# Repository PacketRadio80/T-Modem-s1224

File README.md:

# T-Modem-s1224

**Prototype Notice:** This repository contains hardware prototypes that have **passed all automated software tests** (unit, integration, stress). **Practical field testing with real radio equipment is still pending.** Use at your own risk. GPLv3 — non-profit.

---

USB KISS half-TNC + softmodem AFSK for Raspberry Pi Pico. No modem chip — all signal processing done in software (PWM TX / ADC Goertzel RX). Six baud rates available as separate firmware images.

**Firmware language:** C · **License:** GPLv3 · **Platform:** RP2040 (Raspberry Pi Pico)

**Docs:** [`docs/dok/README.md`](docs/dok/README.md) — complete documentation (build · flash · commission · operate · host · troubleshooting).

## Firmware Images

Pre-built UF2 files in `firmware/s1224/bin/`:

| File | Baud | Mark (Hz) | Space (Hz) | Profile |
|------|------|-----------|------------|---------|
| `s1224-300.uf2` | 300 | 1600 | 1800 | HF narrow AFSK |
| `s1224-600.uf2` | 600 | 1200 | 1800 | HF standard |
| `s1224-1200.uf2` | 1200 | 1200 | 2200 | Bell-202 |
| `s1224-2400.uf2` | 2400 | 1775 | 3250 | Y2-class |
| `s1224-3600.uf2` | 3600 | 1800 | 2700 | High-rate HF |
| `s1224-4800.uf2` | 4800 | 2100 | 3300 | High-rate |

Each baud rate requires a **separate firmware image** — no runtime switching.

## Quick Guide — Firmware Update

### Prerequisites
- Raspberry Pi Pico with USB cable
- T-Modem-s1224 board (or any RP2040 board for testing)

### Flash via BOOTSEL (Recommended)

1. **Disconnect** the Pico from USB.
2. **Hold the BOOTSEL button** on the Pico while plugging in USB.
3. The Pico appears as a USB mass storage device (`RPI-RP2`).
4. **Copy** the appropriate `.uf2` file to the `RPI-RP2` drive:
   ```bash
   # Linux
   cp firmware/s1224/bin/s1224-2400.uf2 /media/$USER/RPI-RP2/
   ```
5. The Pico **automatically reboots** and runs the new firmware.
6. Verify: open `/dev/ttyACM0` at 115200 baud, send `STATUS` → should respond.

### Flash via picotool (Advanced)

```bash
picotool load firmware/s1224/bin/s1224-2400.uf2 -x
```

**Unattended (CLI):** send `BOOTSEL` (or `DFU`) to enter the UF2 bootloader, `REBOOT` to restart. Opening the port at **1200 baud** and dropping **DTR** also enters the bootloader (classic 1200bps touch).

### Build from Source

```bash
export PICO_SDK_PATH=/path/to/pico-sdk
cd firmware/s1224
mkdir build && cd build
cmake .. -DS1224_BITRATE=2400   # 300|600|1200|2400|3600|4800
make -j$(nproc)
# → s1224-2400.uf2
```

## Operation

1. Power from **12 V** barrel (centre-positive). USB = data only.
2. Connect USB to host. Open `/dev/ttyACM0` at 115200 baud.
3. **KISS mode:** Send `0xC0`-framed packets (standard KISS TNC).
4. **Service mode:** Send ASCII commands (`HELP`, `STATUS`, `PTT ON/OFF`, `ID`).

### ASCII Commands

| Command | Description |
|---------|-------------|
| `HELP` | List available commands |
| `STATUS` | Show modem state, PTT, signal, bitrate |
| `ID` | Show device ID, callsign, bitrate |
| `PTT ON` / `PTT OFF` | Manual PTT control |
| `QUIET ON/OFF` | Enable/disable unsolicited output |
| `INI` | Dump configuration |
| `GET <key>` | Read config value |
| `SET <key>=<value>` | Set config value (RAM only) |
| `SAVE` | Persist config to flash |
| `RELOAD` | Reload config from flash |
| `DEFAULTS` | Reset to factory defaults |
| `BOOTSEL` / `DFU` | Enter UF2 bootloader (unattended flash) |
| `REBOOT` | Restart the firmware |

## Hardware

- **Schematic:** `hardware/kicad/`
- **BOM:** `hardware/BOM.md` and `hardware/bom/BOM.csv`
- **AF out:** GP6 (PWM AFSK output)
- **AF in:** GP26 (ADC Goertzel input)
- **PTT:** GP9 → optocoupler → radio PTT input
- **Display:** I2C HD44780 via PCF8574 backpack (optional)
- **Missing component (nachrüstbar):** the TX AF output buffer is not populated on the shared AF stage. **Retrofit (Lösung 1):** unity-gain op-amp buffer between the AF source and `RV1` — improves TX audio (required on the c1224's weak TCM3105 `TXA`; optional here since GP6 PWM is a stronger driver).

## Architecture

```
Host (USB CDC) ←→ Pico (RP2040) ←→ Radio
                  │
                  ├── KISS parser (0xC0 framing)
                  ├── HDLC encode/decode
                  ├── AFSK softmodem (PWM TX / Goertzel RX)
                  ├── PTT control (GP9)
                  ├── I2C display (optional)
                  └── Config (flash storage)
```

## Tone Profiles (Compile-Time)

| Baud | Mark (Hz) | Space (Hz) | Shift (Hz) | Notes |
|------|-----------|------------|------------|-------|
| 300 | 1600 | 1800 | 200 | HF narrow |
| 600 | 1200 | 1800 | 600 | HF standard |
| 1200 | 1200 | 2200 | 1000 | Bell-202 |
| 2400 | 1775 | 3250 | 1475 | Y2-class |
| 3600 | 1800 | 2700 | 900 | High-rate HF |
| 4800 | 2100 | 3300 | 1200 | High-rate |

## Project Structure

```
T-Modem-s1224/
├── firmware/s1224/
│   ├── src/common/          # C source files
│   ├── include/             # Headers (afsk_soft.h, afsk_profile.h)
│   ├── config/              # Default INI
│   ├── bin/                 # Pre-built UF2 images (6 rates)
│   └── CMakeLists.txt
├── hardware/
│   ├── kicad/               # Schematic + PCB
│   ├── bom/                 # Bill of materials
│   └── BOM.md
├── docs/                    # User guide, figures
└── share/                   # Example INI files
```

## License

GNU General Public License v3.0 — see [LICENSE](LICENSE).

**Non-profit project.** Not for commercial use without permission.

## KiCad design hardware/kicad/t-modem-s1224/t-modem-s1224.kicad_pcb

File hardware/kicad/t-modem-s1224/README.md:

# KiCad — T-Modem-s1224

Same PCB base as **T-Modem-c1224**, softmodem stuffing / metadata variant.

| File | Role |
|------|------|
| `t-modem-s1224.kicad_sch` | Schematic (chip symbols **DNP**) |
| `t-modem-s1224.kicad_pcb` | PCB **180×180 mm** · **0** tracks · **0** vias |
| `t-modem-s1224.kicad_pro` | Project · `PROJECT=T-Modem-s1224` · `VERSION=1.0-upcoming1` |
| `t-modem-s1224.kicad_sym` | Symbols |
| `t-modem-s1224.rules` | Custom DRC rules |
| `t-modem-s1224.pre-strip-backup.kicad_pcb` | Pre first strip (289 segments) |
| `t-modem-s1224.2026-08-03-pre-reroute-backup.kicad_pcb` | Pre second strip / re-route reset (199 segments) |

## Inventory — PCB footprints (**31**)

**Keep:** U1 Pico · J_DC / U_REG / D_OR1 / F1 / C_BULK / C_BYP* / C_IN · J_AF · Q1 / R_PTT · J_LCD_I2C / U_LVL / RV2 · J_USB / J_USB_PICO · LED_* / R_LED* · SW1 / TP_BOOTSEL · H1–H4.

**Removed (softmodem — not on PCB):**

| Ref | Role |
|-----|------|
| **U_MODEM** / **SKT_MODEM** | TCM3105 + socket (sch **DNP** only) |
| **Y1** / **Y2** / **C_Y*** | Pierce (sch **DNP**) |
| **RV1** / **C_TX** / **C_RX** | Chip-era AF trim / coupling — **DNP** |
| **RV_CDL** / **R_TXR*** / **R_TRS** | Chip straps |

## Schematic DNP (not stuffed)

| Ref | Value | Flags |
|-----|-------|-------|
| **U_MODEM** | TCM3105 | `dnp` · `in_bom no` · `on_board no` |
| **Y1** | 4.4336 MHz | same |
| **Y2** | 6.5536 MHz | same |
| **D_OR2** | DNI-no-VBUS-OR | same (USB VBUS OR unused) |

Tracks (`segment`): **0** — stripped 2026-08-03 for clean re-route.

## U1 Pico AF nets (s1224 — no chip-era `MODEM_*` names)

| Pad | GPIO | Net | Role |
|-----|------|-----|------|
| **9** | GP6 | **`AF_TX`** | PWM AFSK TX → radio AF inject |
| **10** | GP7 | *(NC)* | Unconnected on board |
| **11** | GP8 | *(NC)* | Unconnected on board |
| **31** | GP26 | **`AF_RX`** | ADC RX ← radio AF |
| **12** | GP9 | **`PTT_DRV`** | PTT keying |

## Connector / power nets (pad names)

| Ref | Nets |
|-----|------|
| **J_AF** | `AF_TX` · `AF_RX` · `PTT_OC` · `GND` |
| **J_DC** | `VIN_12` · `GND` ×2 |
| **F1** | `+5V_REG` → `+5V` |
| **D_OR1** | `+5V_OR` ← `+5V` |
| **Q1** / **R_PTT** | `PTT_DRV` → `PTT_B` → `PTT_OC` |

No **`MODEM_*`** · **`TXA`** · **`RXA`** · **`TX_LVL`** on PCB.

## Prototype AF wiring

- **GP6** PWM AFSK out → `AF_TX` → radio inject
- **GP26** ADC0 ← `AF_RX` ← radio RX AF
- **GP9** PTT → `PTT_DRV`

**AS-IS** · GPLv3 · non-profit.

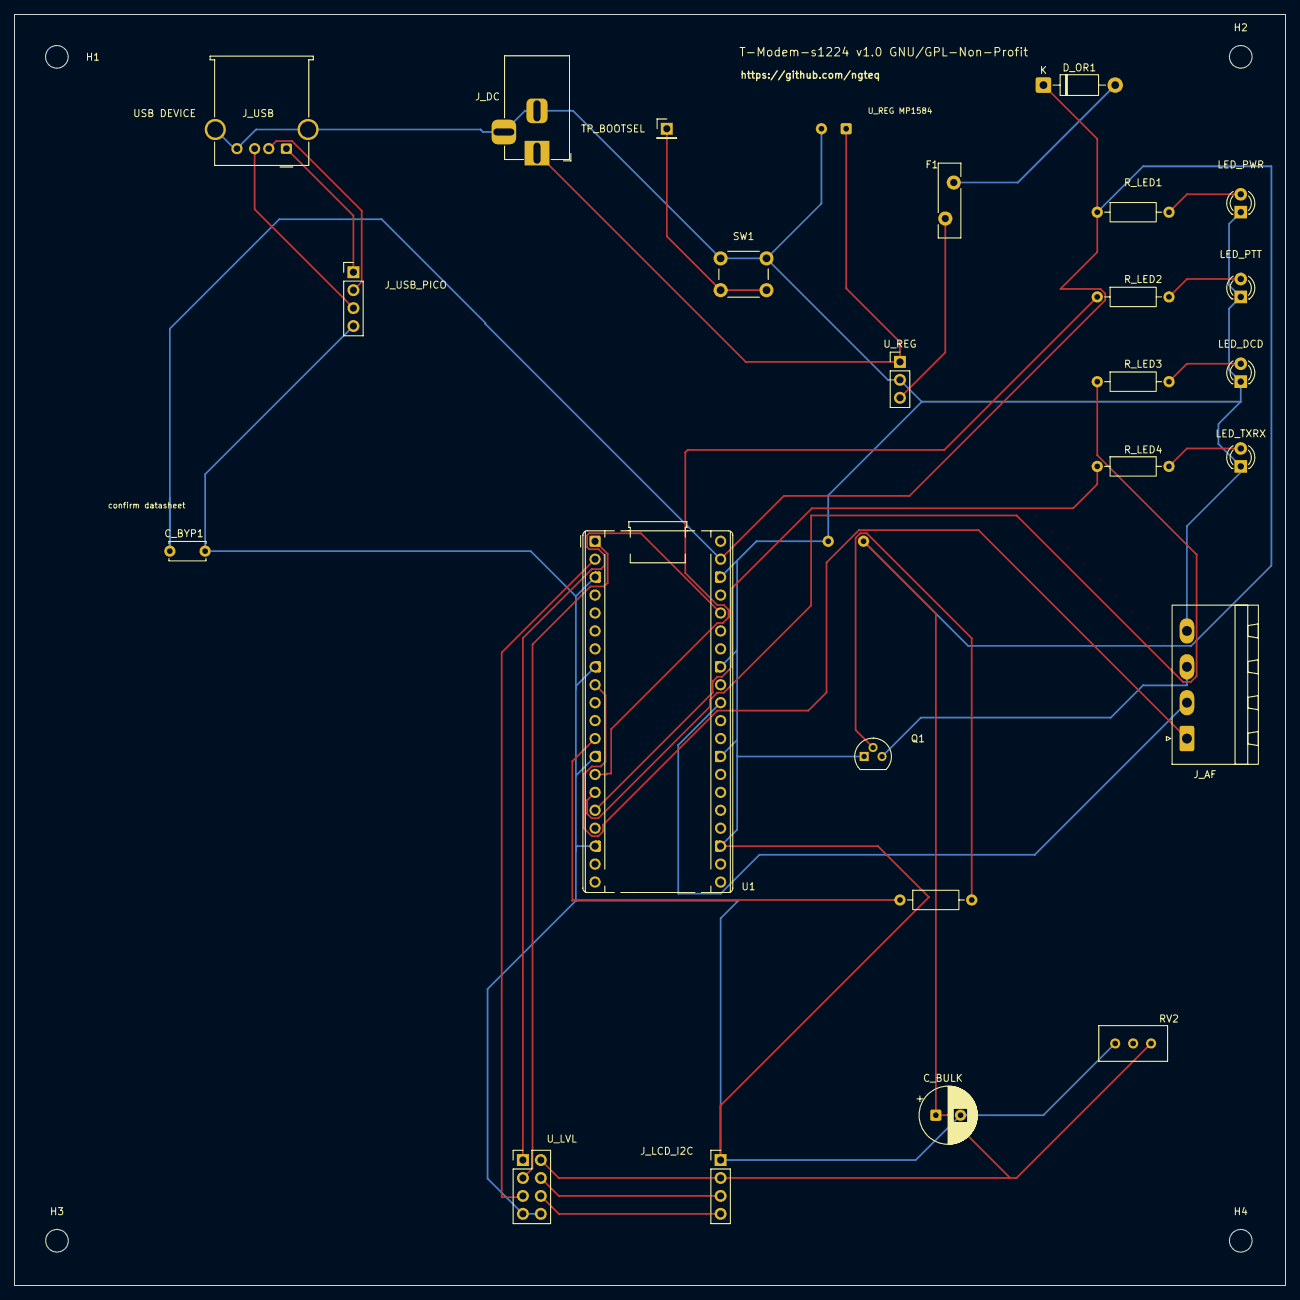
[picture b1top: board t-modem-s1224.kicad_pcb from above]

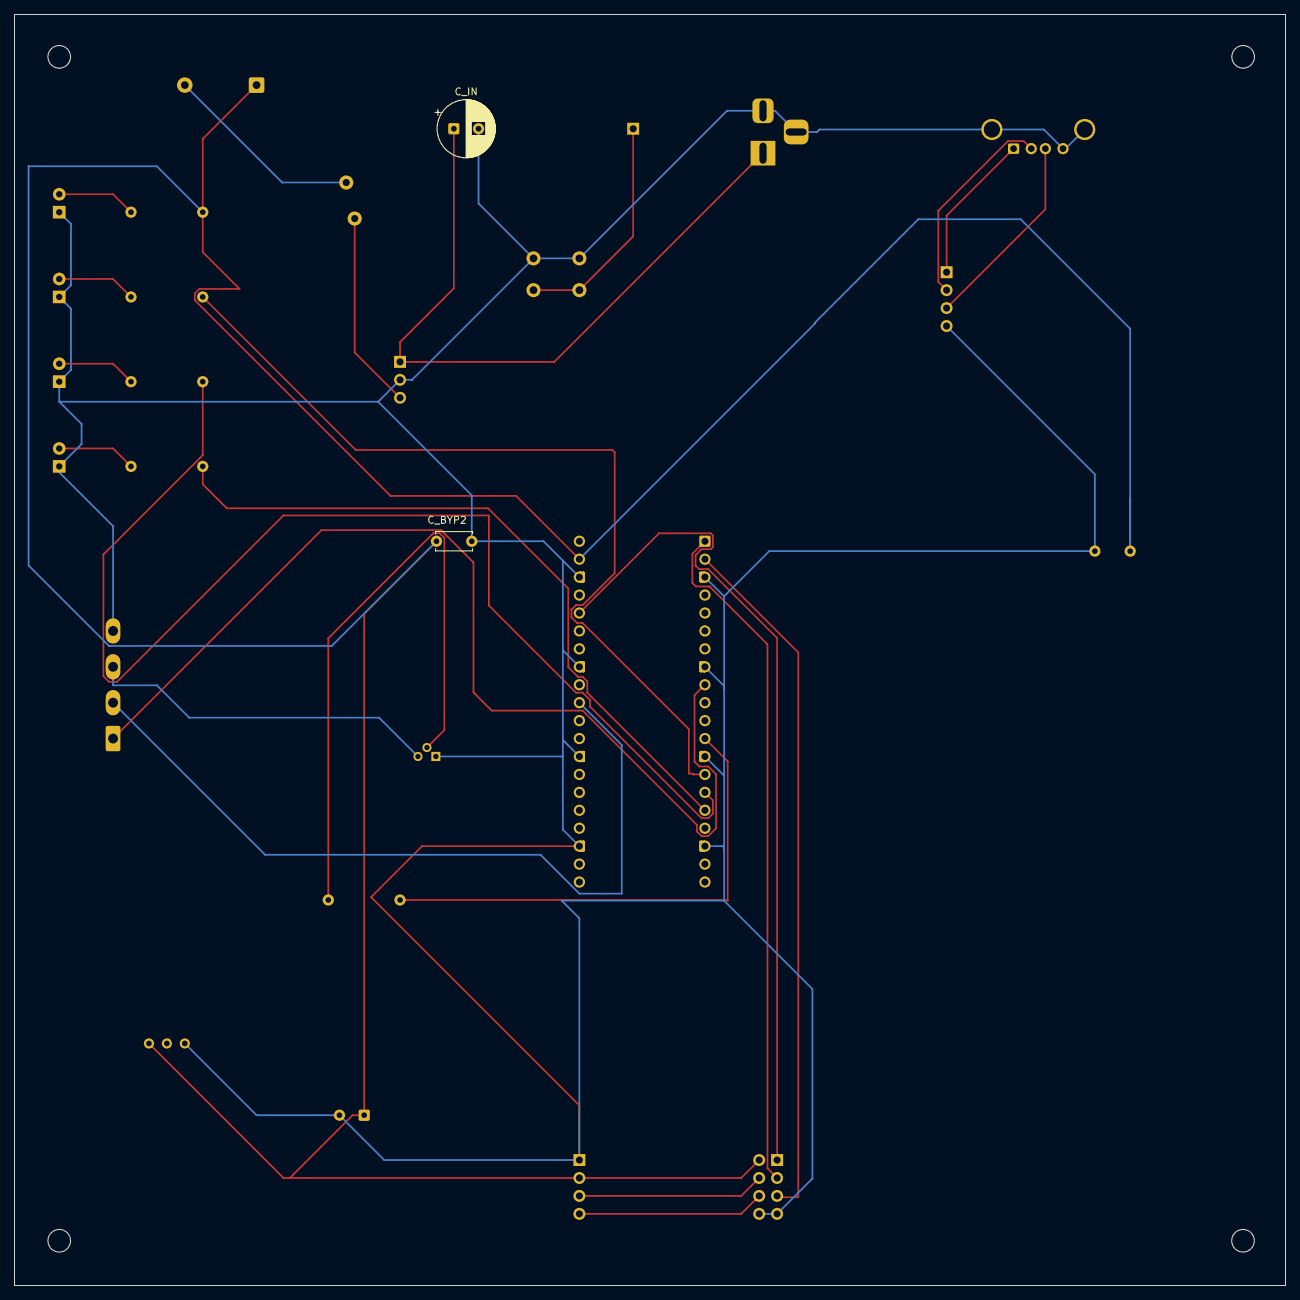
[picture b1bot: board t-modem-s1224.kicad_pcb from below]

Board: 2 copper layers, 180.0 x 180.0 mm, 31 parts (2 on the bottom side), 26 nets.

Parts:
C_BULK: 100uF; CP_Radial_D8.0mm_P3.50mm
C_BYP1, C_BYP2: 100nF; C_Disc_D5.0mm_W2.5mm_P5.00mm
C_IN: 100uF; CP_Radial_D8.0mm_P3.50mm
D_OR1: 1N5819; D_DO-41_SOD81_P10.16mm_Horizontal
F1: MF-RG500; Fuse_Bourns_MF-RG500
H1, H2, H3, H4: M3; MountingHole_3.2mm_M3
J_AF: AF; PhoenixContact_MSTBA_2,5_4-G-5,08_1x04_P5.08mm_Horizontal
J_DC: 12V CENTRE; BarrelJack_Horizontal
J_LCD_I2C: LCD I2C; PinHeader_1x04_P2.54mm_Vertical
J_USB: USB_A; USB_A_Molex_67643_Horizontal
J_USB_PICO: Pico Micro-USB cable; PinHeader_1x04_P2.54mm_Vertical
LED_DCD: DCD; LED_D3.0mm
LED_PTT: PTT; LED_D3.0mm
LED_PWR: PWR; LED_D3.0mm
LED_TXRX: TXRX; LED_D3.0mm
Q1: 2N2222A; TO-92
RV2: 10k contrast; Potentiometer_Bourns_3296W_Vertical
R_LED1, R_LED2, R_LED3, R_LED4: 1k; R_Axial_DIN0207_L6.3mm_D2.5mm_P10.16mm_Horizontal
R_PTT: 4.7k; R_Axial_DIN0207_L6.3mm_D2.5mm_P10.16mm_Horizontal
SW1: BOOTSEL; SW_PUSH_6mm
TP_BOOTSEL: Pico BOOTSEL; PinHeader_1x01_P2.54mm_Vertical
U1: RPi-Pico; RaspberryPi_Pico_Common_THT
U_LVL: BSS138; PinHeader_2x04_P2.54mm_Vertical
U_REG: Mini560-5V; PinHeader_1x03_P2.54mm_Vertical

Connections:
3V3: U1.36, U_LVL.1
+5V: D_OR1.2, F1.2
+5V_OR: C_BULK.1, C_BYP1.1, C_BYP2.1, D_OR1.1, J_LCD_I2C.2, RV2.1, R_LED1.1, U1.39, U_LVL.2
+5V_REG: F1.1, U_REG.3
AF_RX: J_AF.2, U1.31
AF_TX: J_AF.1, U1.9
BOOTSEL: SW1.2, TP_BOOTSEL.1
GND: C_BULK.2, C_BYP1.2, C_BYP2.2, C_IN.2, J_AF.4, J_DC.2, J_DC.3, J_LCD_I2C.1, J_USB.4, J_USB.SH, J_USB_PICO.4, LED_DCD.1, LED_PTT.1, LED_PWR.1, LED_TXRX.1, Q1.1, RV2.3, SW1.1, U1.3, U1.8, U1.13, U1.18, U1.23, U1.28, U1.33, U1.38, U_LVL.7, U_LVL.8, U_REG.2
I2C_SCL_3V3: U1.2, U_LVL.5
I2C_SCL_5V: J_LCD_I2C.4, U_LVL.6
I2C_SDA_3V3: U1.1, U_LVL.3
I2C_SDA_5V: J_LCD_I2C.3, U_LVL.4
LED_DCD_A: LED_DCD.2, R_LED3.2
LED_DCD_N: R_LED3.1, U1.15
LED_PTT_A: LED_PTT.2, R_LED2.2
LED_PTT_N: R_LED2.1, U1.14
LED_PWR_A: LED_PWR.2, R_LED1.2
LED_TXRX_A: LED_TXRX.2, R_LED4.2
LED_TXRX_N: R_LED4.1, U1.16
PTT_B: Q1.2, R_PTT.2
PTT_DRV: R_PTT.1, U1.12
PTT_OC: J_AF.3, Q1.3
USB_DM: J_USB.2, J_USB_PICO.2
USB_DP: J_USB.3, J_USB_PICO.3
USB_VBUS_NC: J_USB.1, J_USB_PICO.1
VIN_12: C_IN.1, J_DC.1, U_REG.1

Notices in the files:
hardware/kicad/t-modem-s1224/t-modem-s1224.kicad_pcb:
GNU/GPLv3-Non-Profit (as-is)
T-Modem-s1224 v1.0 GNU/GPL-Non-Profit
